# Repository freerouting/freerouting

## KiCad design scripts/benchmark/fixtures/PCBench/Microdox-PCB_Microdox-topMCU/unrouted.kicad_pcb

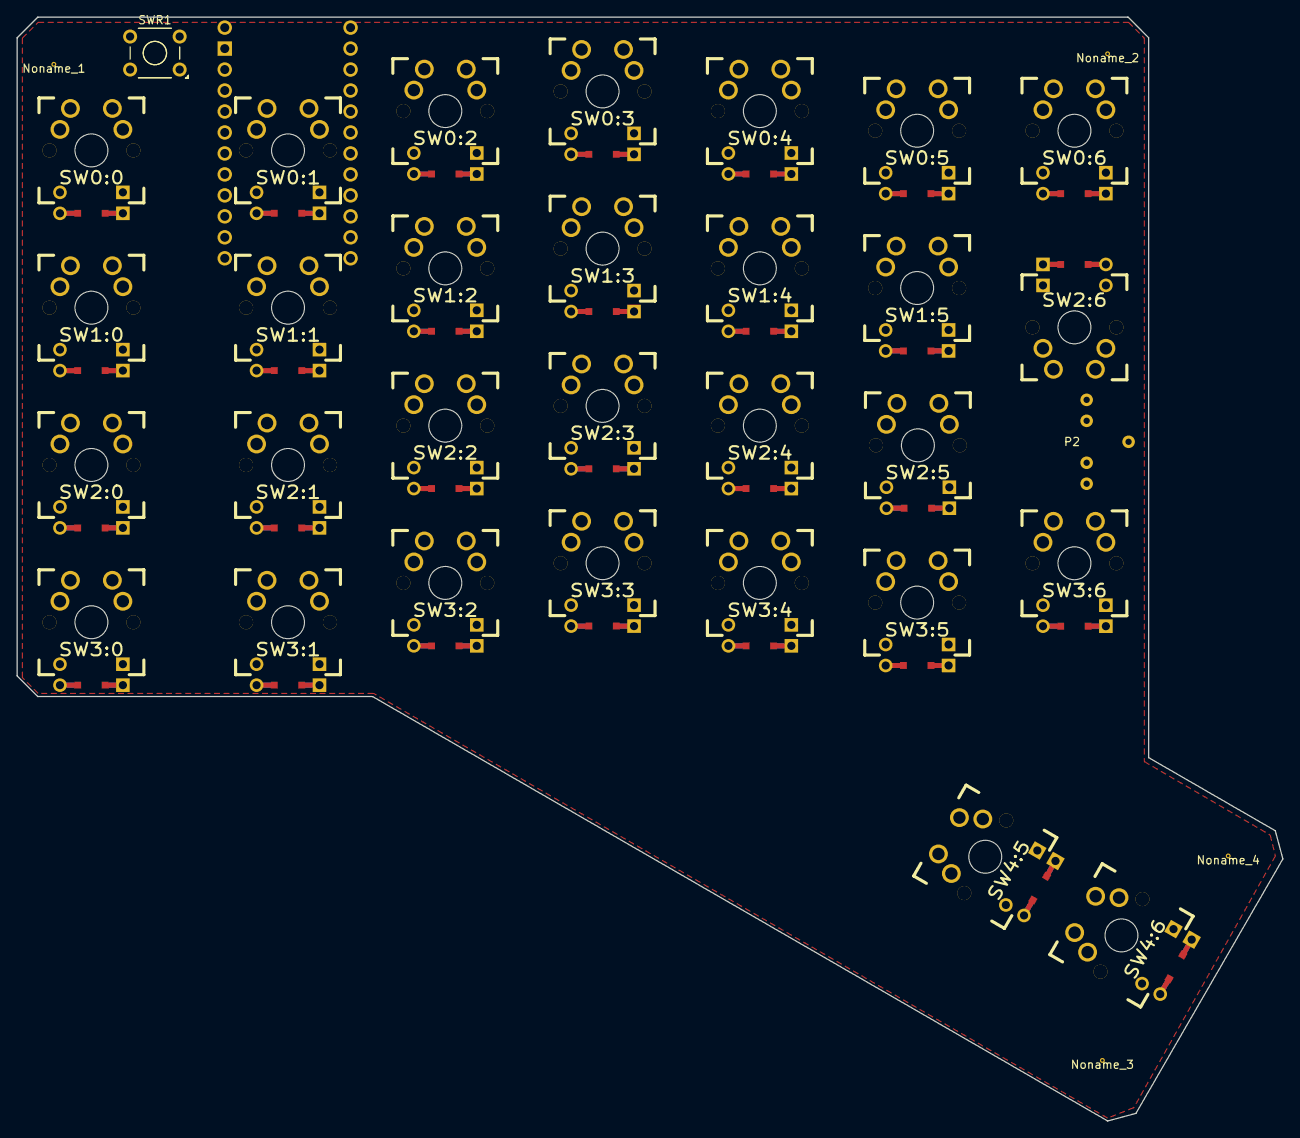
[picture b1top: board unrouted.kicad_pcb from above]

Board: 2 copper layers, 153.3 x 133.7 mm, 36 parts (1 on the bottom side), 45 nets, no tracks yet.

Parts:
Noname_1, Noname_2, Noname_3, Noname_4: VIA-0.6
P2: CONN_01X03; 3mmJack
PM1: PROMICRO
SW0:0, SW0:1, SW0:2, SW0:3, SW0:4, SW0:5, SW0:6, SW1:0, SW1:1, SW1:2, SW1:3, SW1:4, SW1:5, SW2:0, SW2:1, SW2:2, SW2:3, SW2:4, SW2:5, SW2:6, SW3:0, SW3:1, SW3:2, SW3:3, SW3:4, SW3:5, SW3:6, SW4:5, SW4:6: MX_FLIP_DIODE
SWR1: SW_PUSH; SW_TH_Tactile_Omron_B3F-10xx

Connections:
/COL0: PM1.16, SW0:0.1, SW1:0.1, SW2:0.1, SW3:0.1
/COL1: PM1.17, SW0:1.1, SW1:1.1, SW2:1.1, SW3:1.1
/COL2: PM1.18, SW0:2.1, SW1:2.1, SW2:2.1, SW3:2.1
/COL3: PM1.20, SW0:3.1, SW1:3.1, SW2:3.1, SW3:3.1
/COL4: PM1.21, SW0:4.1, SW1:4.1, SW2:4.1, SW3:4.1
/COL5: PM1.11, SW0:5.1, SW1:5.1, SW2:5.1, SW3:5.1, SW4:5.1
/COL6: PM1.23, SW0:6.1, SW2:6.1, SW3:6.1, SW4:6.1
/ROW0: PM1.9, SW0:0.4, SW0:1.4, SW0:2.4, SW0:3.4, SW0:4.4, SW0:5.4, SW0:6.4
/ROW1: PM1.8, SW1:0.4, SW1:1.4, SW1:2.4, SW1:3.4, SW1:4.4, SW1:5.4, SW2:6.4
/ROW2: PM1.7, SW2:0.4, SW2:1.4, SW2:2.4, SW2:3.4, SW2:4.4, SW2:5.4
/ROW3: PM1.6, SW3:0.4, SW3:1.4, SW3:2.4, SW3:3.4, SW3:4.4, SW3:5.4, SW3:6.4
/ROW4: PM1.10, SW4:5.4, SW4:6.4
/RST: PM1.14, SWR1.1
/SER: P2.2, PM1.5
GND: Noname_1.1, Noname_2.1, Noname_3.1, Noname_4.1, P2.3, PM1.2, PM1.3, PM1.13, SWR1.2
unnamed: SW0:0.2, SW0:0.3
unnamed: SW0:1.2, SW0:1.3
unnamed: SW0:2.2, SW0:2.3
unnamed: SW0:3.2, SW0:3.3
unnamed: SW0:4.2, SW0:4.3
unnamed: SW0:5.2, SW0:5.3
unnamed: SW0:6.2, SW0:6.3
unnamed: SW1:0.2, SW1:0.3
unnamed: SW1:1.2, SW1:1.3
unnamed: SW1:2.2, SW1:2.3
unnamed: SW1:3.2, SW1:3.3
unnamed: SW1:4.2, SW1:4.3
unnamed: SW1:5.2, SW1:5.3
unnamed: SW2:0.2, SW2:0.3
unnamed: SW2:1.2, SW2:1.3
unnamed: SW2:2.2, SW2:2.3
unnamed: SW2:3.2, SW2:3.3
unnamed: SW2:4.2, SW2:4.3
unnamed: SW2:5.2, SW2:5.3
unnamed: SW2:6.2, SW2:6.3
unnamed: SW3:0.2, SW3:0.3
unnamed: SW3:1.2, SW3:1.3
unnamed: SW3:2.2, SW3:2.3
unnamed: SW3:3.2, SW3:3.3
unnamed: SW3:4.2, SW3:4.3
unnamed: SW3:5.2, SW3:5.3
unnamed: SW3:6.2, SW3:6.3
unnamed: SW4:5.2, SW4:5.3
unnamed: SW4:6.2, SW4:6.3
VCC: P2.1, PM1.15
